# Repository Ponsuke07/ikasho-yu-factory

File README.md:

View this project on [CADLAB.io](https://cadlab.io/project/1048). 

# ikasho-yu-factory

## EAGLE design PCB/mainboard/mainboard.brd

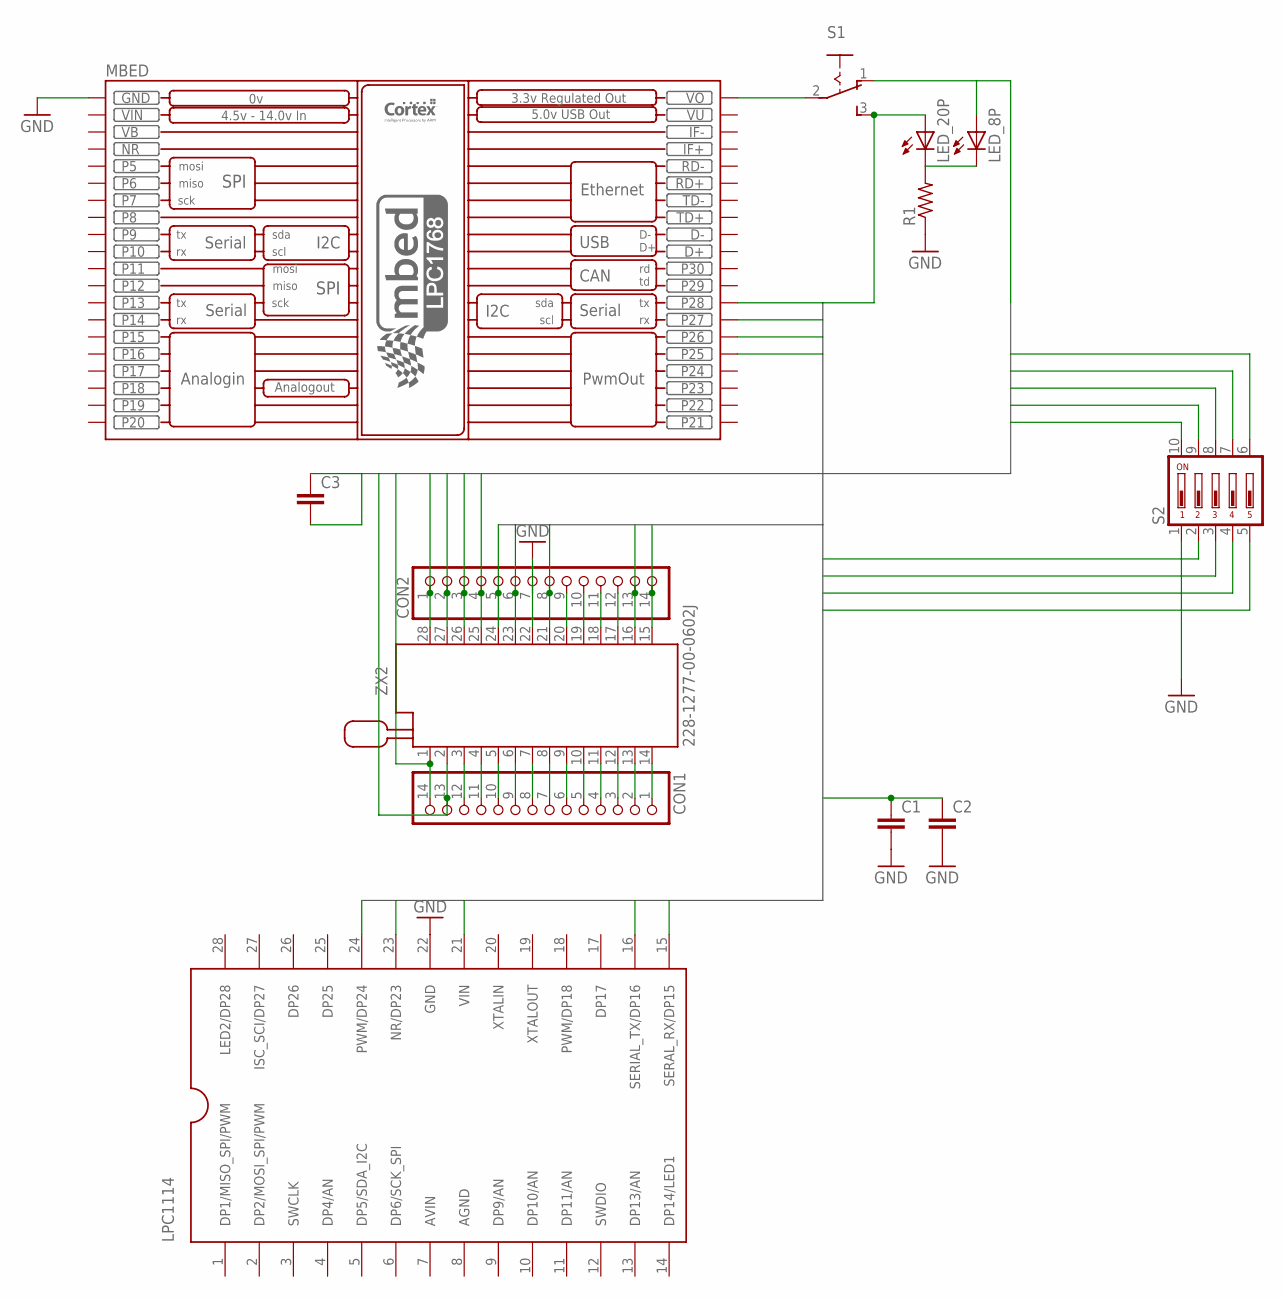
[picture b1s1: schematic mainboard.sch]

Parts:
C1, C2, C3: C-EUC2012; C2012
CON1, CON2: PINHD-1X14; 1X14
LED_8P, LED_20P: LED3MM
LPC1114: LPC1114FDH28; TSSOP28
MBED: MBED_NXP_LPC1768; MBED-KIT
R1: R-US_0207/10; 0207/10
S1: M251
S2: DIP05YL
ZX2: 228-1277-00-0602J

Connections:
AGND: LPC1114.8 (AGND)
AVIN: LPC1114.7 (AVIN)
BUS0: C1.1, C2.1, CON2.8, LED_20P.A, LPC1114.21 (VIN), S1.3 (S), ZX2.21
BUS2: CON2.14, LPC1114.15 (SERAL_RX/DP15), MBED.P$28 (P28), S2.2, ZX2.15
BUS3: CON2.13, LPC1114.16 (SERIAL_TX/DP16), MBED.P$27 (P27), S2.5, ZX2.16
BUS4: CON2.6, LPC1114.23 (NR/DP23), MBED.P$26 (P26), S2.4, ZX2.23
BUS5: CON2.5, LPC1114.24 (PWM/DP24), MBED.P$25 (P25), S2.3, ZX2.24
BUS8P0: C3.1, CON2.3, LED_8P.A, S1.1 (O), ZX2.26
BUS8P1: C3.2, CON2.2, S2.10, ZX2.27
BUS8P2: CON2.1, S2.9, ZX2.28
BUS8P3: CON1.14, S2.6, ZX2.1
BUS8P4: CON1.13, S2.7, ZX2.2
BUS8P5: CON2.4, S2.8, ZX2.25
GND: C1.2, C2.2, CON2.7, LPC1114.22 (GND), MBED.GND, R1.1, S2.1, ZX2.22
unnamed: MBED.VOUT (VO), S1.2
unnamed: LED_8P.K (C), LED_20P.K (C), R1.2
unnamed: CON1.1, ZX2.14
unnamed: CON1.2, ZX2.13
unnamed: CON1.3, ZX2.12
unnamed: CON1.4, ZX2.11
unnamed: CON1.5, ZX2.10
unnamed: CON1.6, ZX2.9
unnamed: CON1.7, ZX2.8
unnamed: CON1.8, ZX2.7
unnamed: CON1.9, ZX2.6
unnamed: CON1.10, ZX2.5
unnamed: CON1.11, ZX2.4
unnamed: CON1.12, ZX2.3
unnamed: CON2.9, ZX2.20
unnamed: CON2.10, ZX2.19
unnamed: CON2.11, ZX2.18
unnamed: CON2.12, ZX2.17
NR: MBED.NR
VB: MBED.VB
VIN: MBED.VIN
VU: MBED.VU

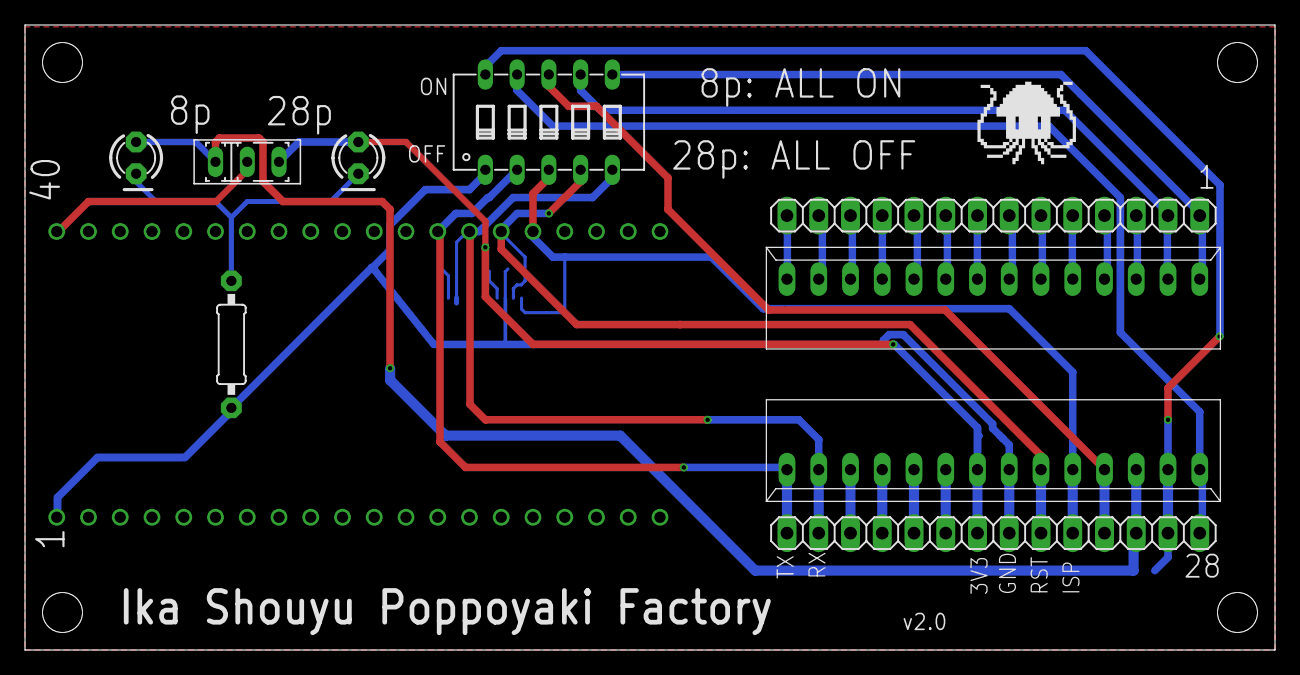
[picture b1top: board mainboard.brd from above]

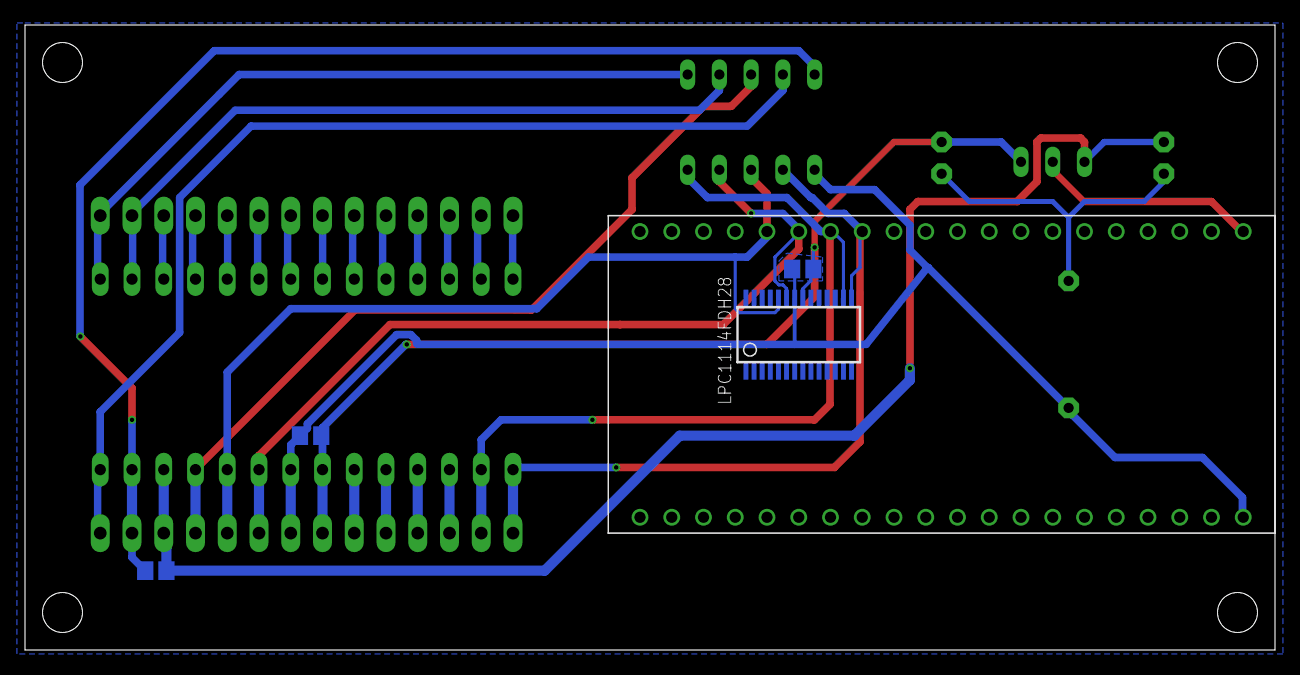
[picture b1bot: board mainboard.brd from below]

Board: 2 copper layers, 100.0 x 50.0 mm, 13 parts (4 on the bottom side), 30 nets.

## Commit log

2017-08-10 Update gitignore for Elecrow cam processor
2017-08-10 Add Eagle libs
2017-08-10 Add mainboard
2017-08-27 Fix fonts and switch.
    This commit will fix two issue.
    First, use the vector font because the true type is different from prited.
    Second, replace the slide switch because we used the wrong one.
2018-04-25 Update the slik
2018-04-25 Update gitignore for openscad
2018-04-25 Fix the position of lpc1114fhd28.
2018-04-25 Add 3D model of the case.
2018-05-17 Backlink to CADLAB.io has been added.
